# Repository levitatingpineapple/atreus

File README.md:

# Atreus

A keyboard with 42 key [Atreus](https://atreus.technomancy.us) layout. Uses [Kailh Choc](http://www.kailh.com/en/Products/Ks/CS/) low profile switches with hot-swap sockets. Compatible with ProMicro type controllers, but designed to be used with [Nice!Nano](https://nicekeyboards.com/nice-nano). Capable of n-key rollover. There is enough spacing between keys to fit all of the commonly available keycaps - transparent, flat and concave.

## Firmware

[Nice!Nano](https://nicekeyboards.com/nice-nano) is best supported by [ZMK](https://zmk.dev) Configuration for this board is hosted in the [levitatingpineapple/atreus-zmk](https://github.com/levitatingpineapple/atreus-zmk) repo.
To build a different keymap - clone the repo and update `.keymap` file as needed.
The firmware will be build using [Build ZMK firmware](https://github.com/levitatingpineapple/atreus-zmk/actions/workflows/build.yml) action.

## Materials

| Name            | Part                             | Size        | Amount |
| --------------- | -------------------------------- | ----------- | ------ |
| Switch          | [CPG135001D0X](docs/switch.pdf)  | -           | 42     |
| Socket          | [CPG135001S30](docs/socket.pdf)  | -           | 42     |
| Diode           | [1N4148](docs/diode.pdf)         | SOD123      | 42     |
| Controller      | [nice!nano](docs/controller.png) | -           | 1      |
| Battery         | XZK 301230                       | 30x12x3.0mm | 1      |
| Bolt            | M2 Hex                           | 4mm         | 8      |
| Machine Headers | Mill-Max                         | 13p 3mm     | 2      |

### PCB

- ⚠️ No power switch for the battery
- For every switch has a diode, soldered where an backlight LED would normally be located, providing n-key rollover.

### Sockets

- The PCB has 1.5mm wide holes for mounting the controller socket. This allows soldering machine headers flush with the board. The nice!nano controller originally ships with low profile headers, which won't fit the battery underneath the controller, if soldered in this manner. Therefore a pair of 3mm tall headers had to be separately ordered.

### Case

- All 3d printing was done with 0.4mm nozzle at 0.2mm layer height from PETG.
- The bottom case is attached using eight 4mm long M2 bolts.
- Added feet using 1mm thick rubber tape

### Led

- In the nice!nano's cover there are two openings for the LEDs. They can be filled with a dab of hot-glue before the print is removed form the bed to get a more diffused look _...for science, you monster._

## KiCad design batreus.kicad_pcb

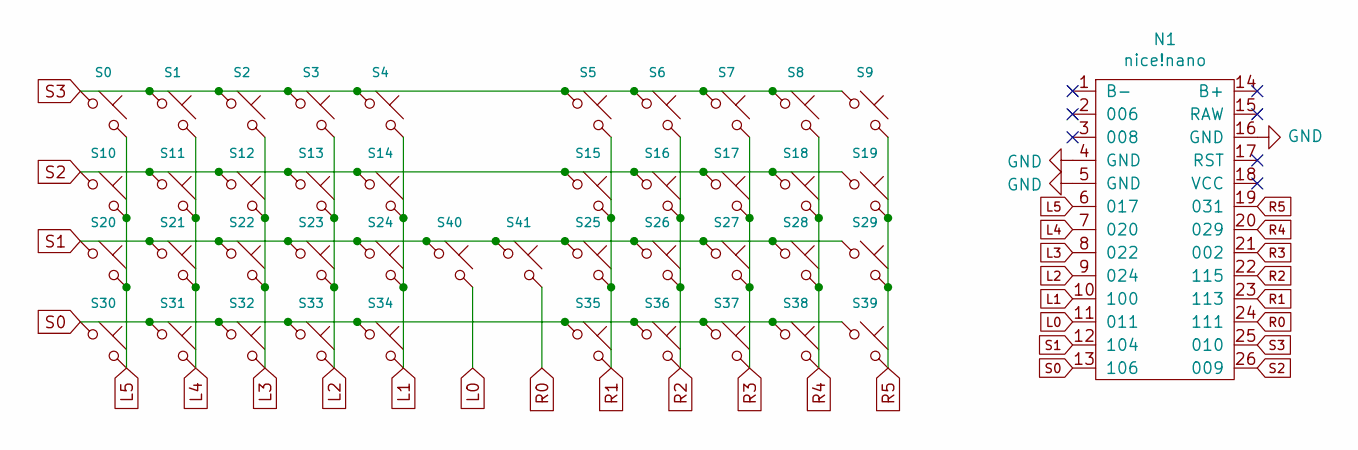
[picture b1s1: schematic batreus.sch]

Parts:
N1: nice!nano
S0, S1, S2, S3, S4, S5, S6, S7, S8, S9, S10, S11, S12, S13, S14, S15, S16, S17, S18, S19, S20, S21, S22, S23, S24, S25, S26, S27, S28, S29, S30, S31, S32, S33, S34, S35, S36, S37, S38, S39, S40, S41: K; HotChoc

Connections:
GND: N1.4 (GND), N1.5 (GND), N1.16 (GND)
L0: N1.11, S40.2
L1: N1.10 (100), S4.2, S14.2, S24.2, S34.2
L2: N1.9 (024), S3.2, S13.2, S23.2, S33.2
L3: N1.8 (022), S2.2, S12.2, S22.2, S32.2
L4: N1.7 (020), S1.2, S11.2, S21.2, S31.2
L5: N1.6 (017), S0.2, S10.2, S20.2, S30.2
R0: N1.24 (111), S41.2
R1: N1.23 (113), S5.2, S15.2, S25.2, S35.2
R2: N1.22 (115), S6.2, S16.2, S26.2, S36.2
R3: N1.21 (002), S7.2, S17.2, S27.2, S37.2
R4: N1.20 (029), S8.2, S18.2, S28.2, S38.2
R5: N1.19 (031), S9.2, S19.2, S29.2, S39.2
S0: N1.13 (106), S30.1, S31.1, S32.1, S33.1, S34.1, S35.1, S36.1, S37.1, S38.1, S39.1
S1: N1.12 (104), S20.1, S21.1, S22.1, S23.1, S24.1, S25.1, S26.1, S27.1, S28.1, S29.1, S40.1, S41.1
S2: N1.26 (009), S10.1, S11.1, S12.1, S13.1, S14.1, S15.1, S16.1, S17.1, S18.1, S19.1
S3: N1.25 (010), S0.1, S1.1, S2.1, S3.1, S4.1, S5.1, S6.1, S7.1, S8.1, S9.1

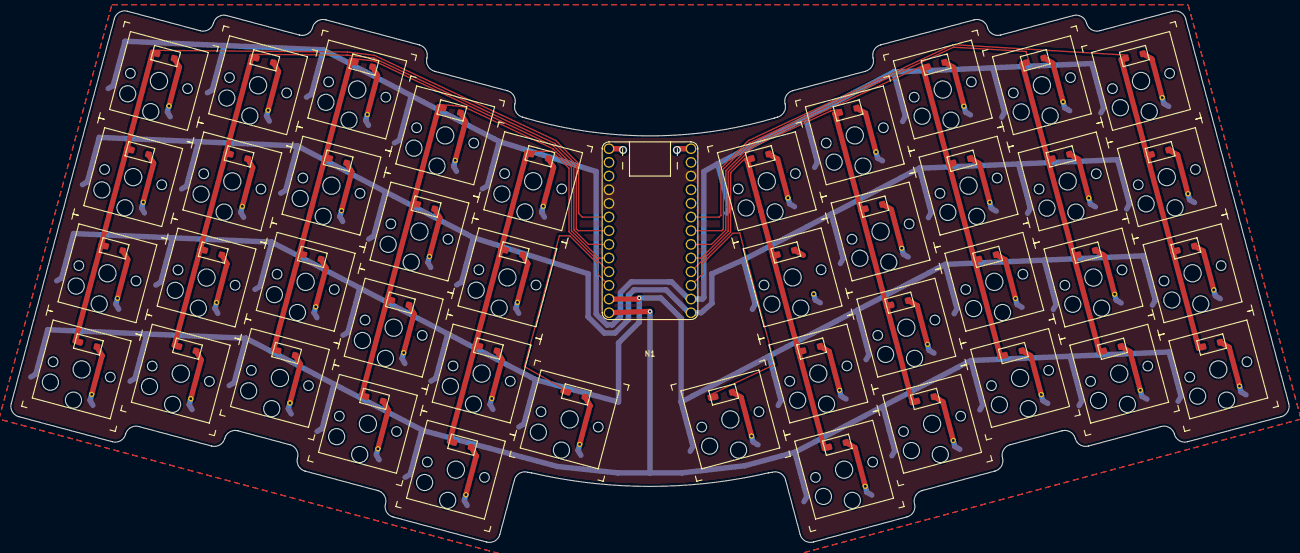
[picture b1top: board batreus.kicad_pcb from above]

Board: 2 copper layers, 237.5 x 98.8 mm, 43 parts (0 on the bottom side), 17 nets.

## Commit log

2020-10-15 add files
2020-10-18 export
2020-10-19 final
2020-10-21 minor
2021-02-13 Add 3d models.
2021-02-27 Add case model
2021-10-02 Reorg
2021-10-02 Add readme
2021-10-02 Spellcheck
2023-02-16 New case. Updated readme
2023-02-16 readme
2023-04-01 Update Readme
    Update markdown to show in the pin.
